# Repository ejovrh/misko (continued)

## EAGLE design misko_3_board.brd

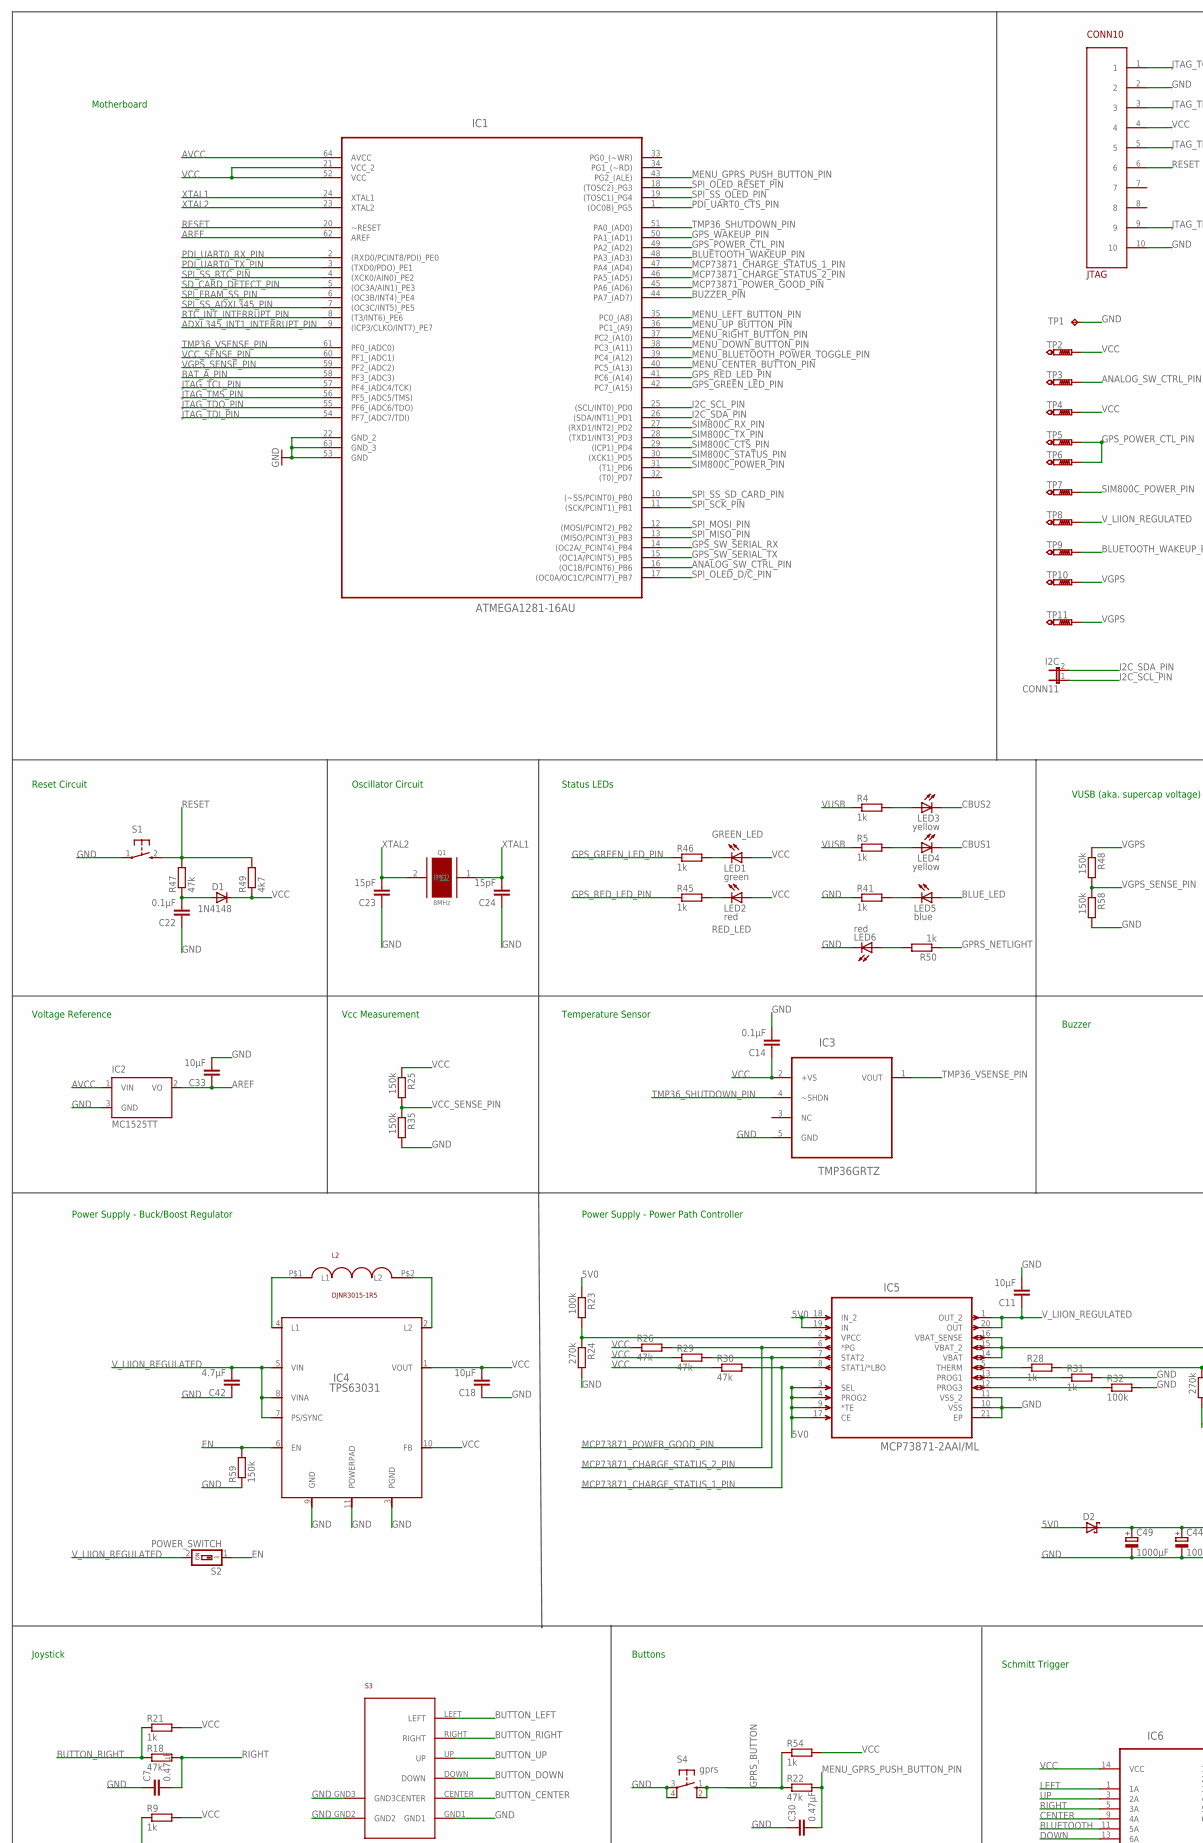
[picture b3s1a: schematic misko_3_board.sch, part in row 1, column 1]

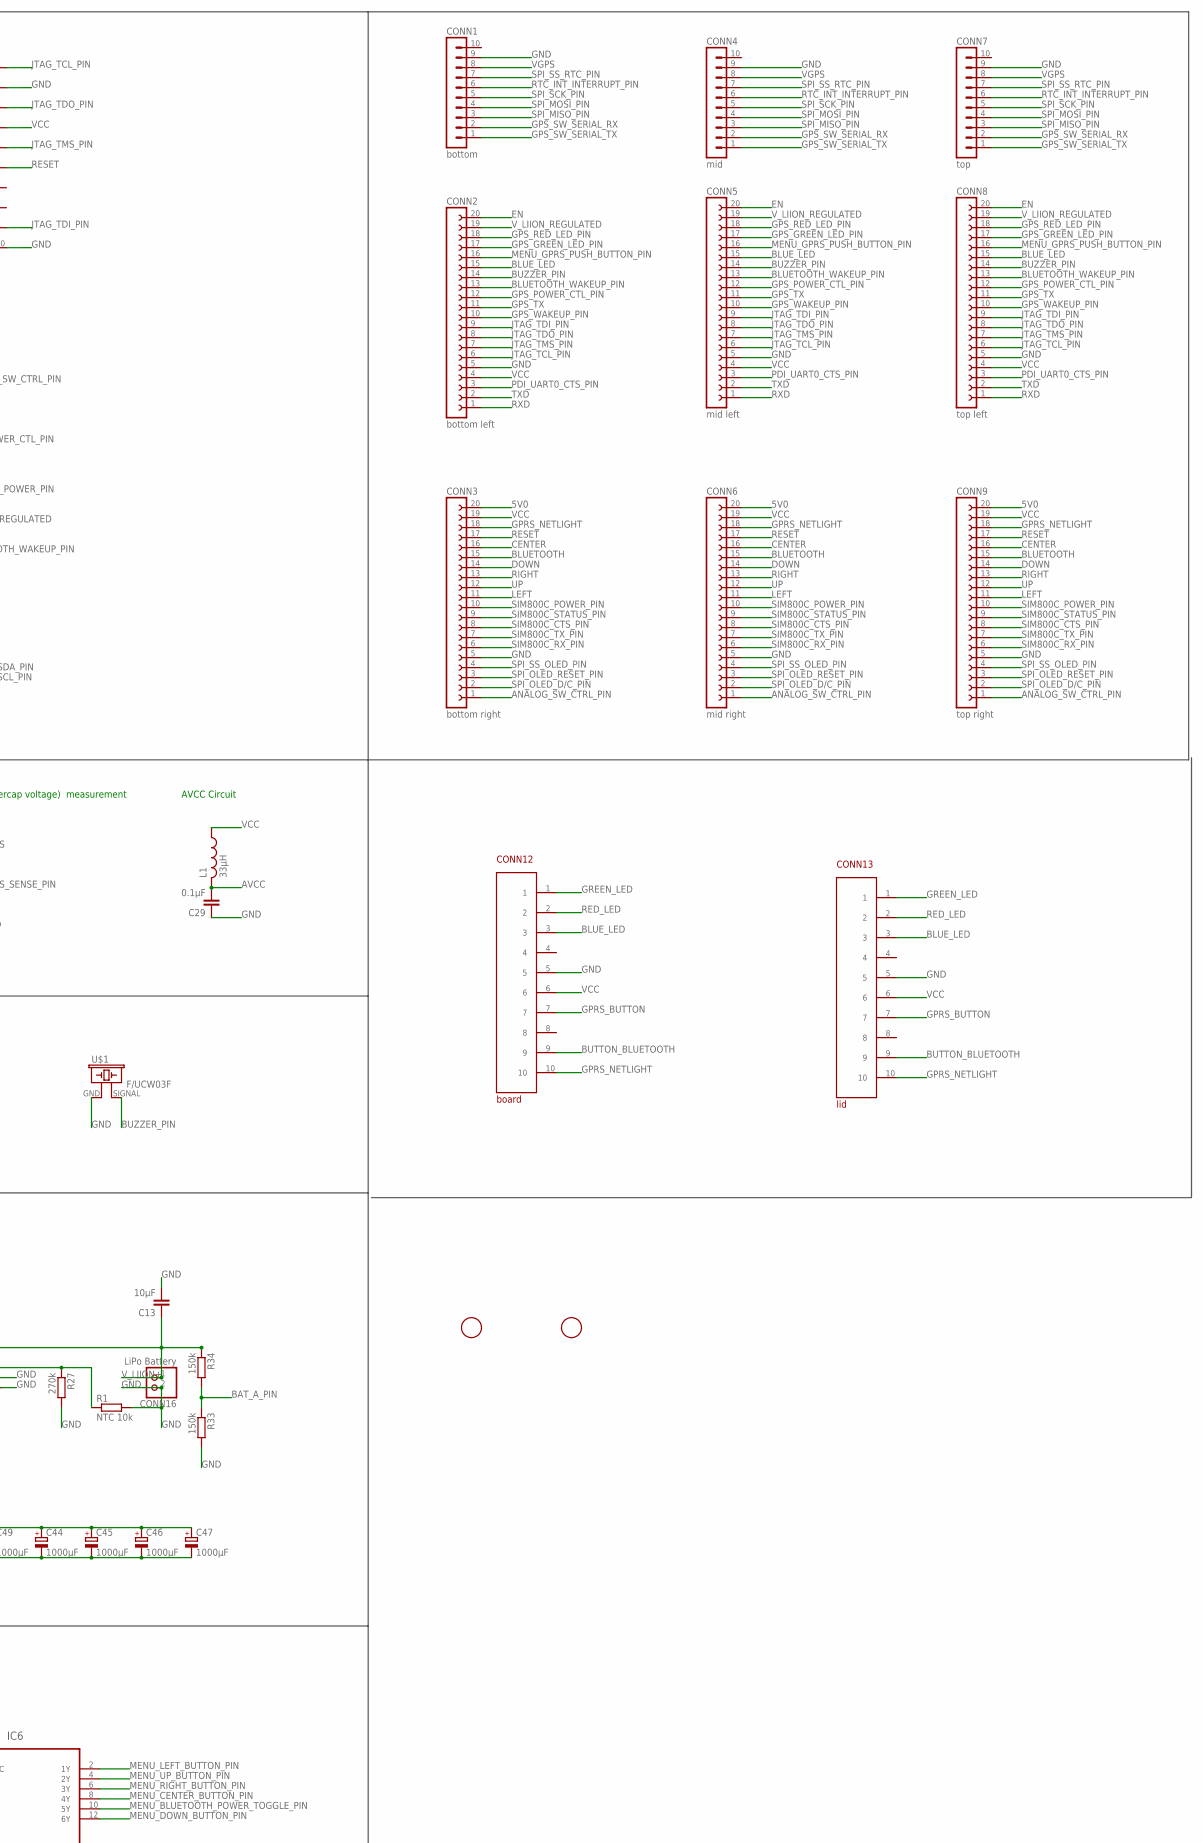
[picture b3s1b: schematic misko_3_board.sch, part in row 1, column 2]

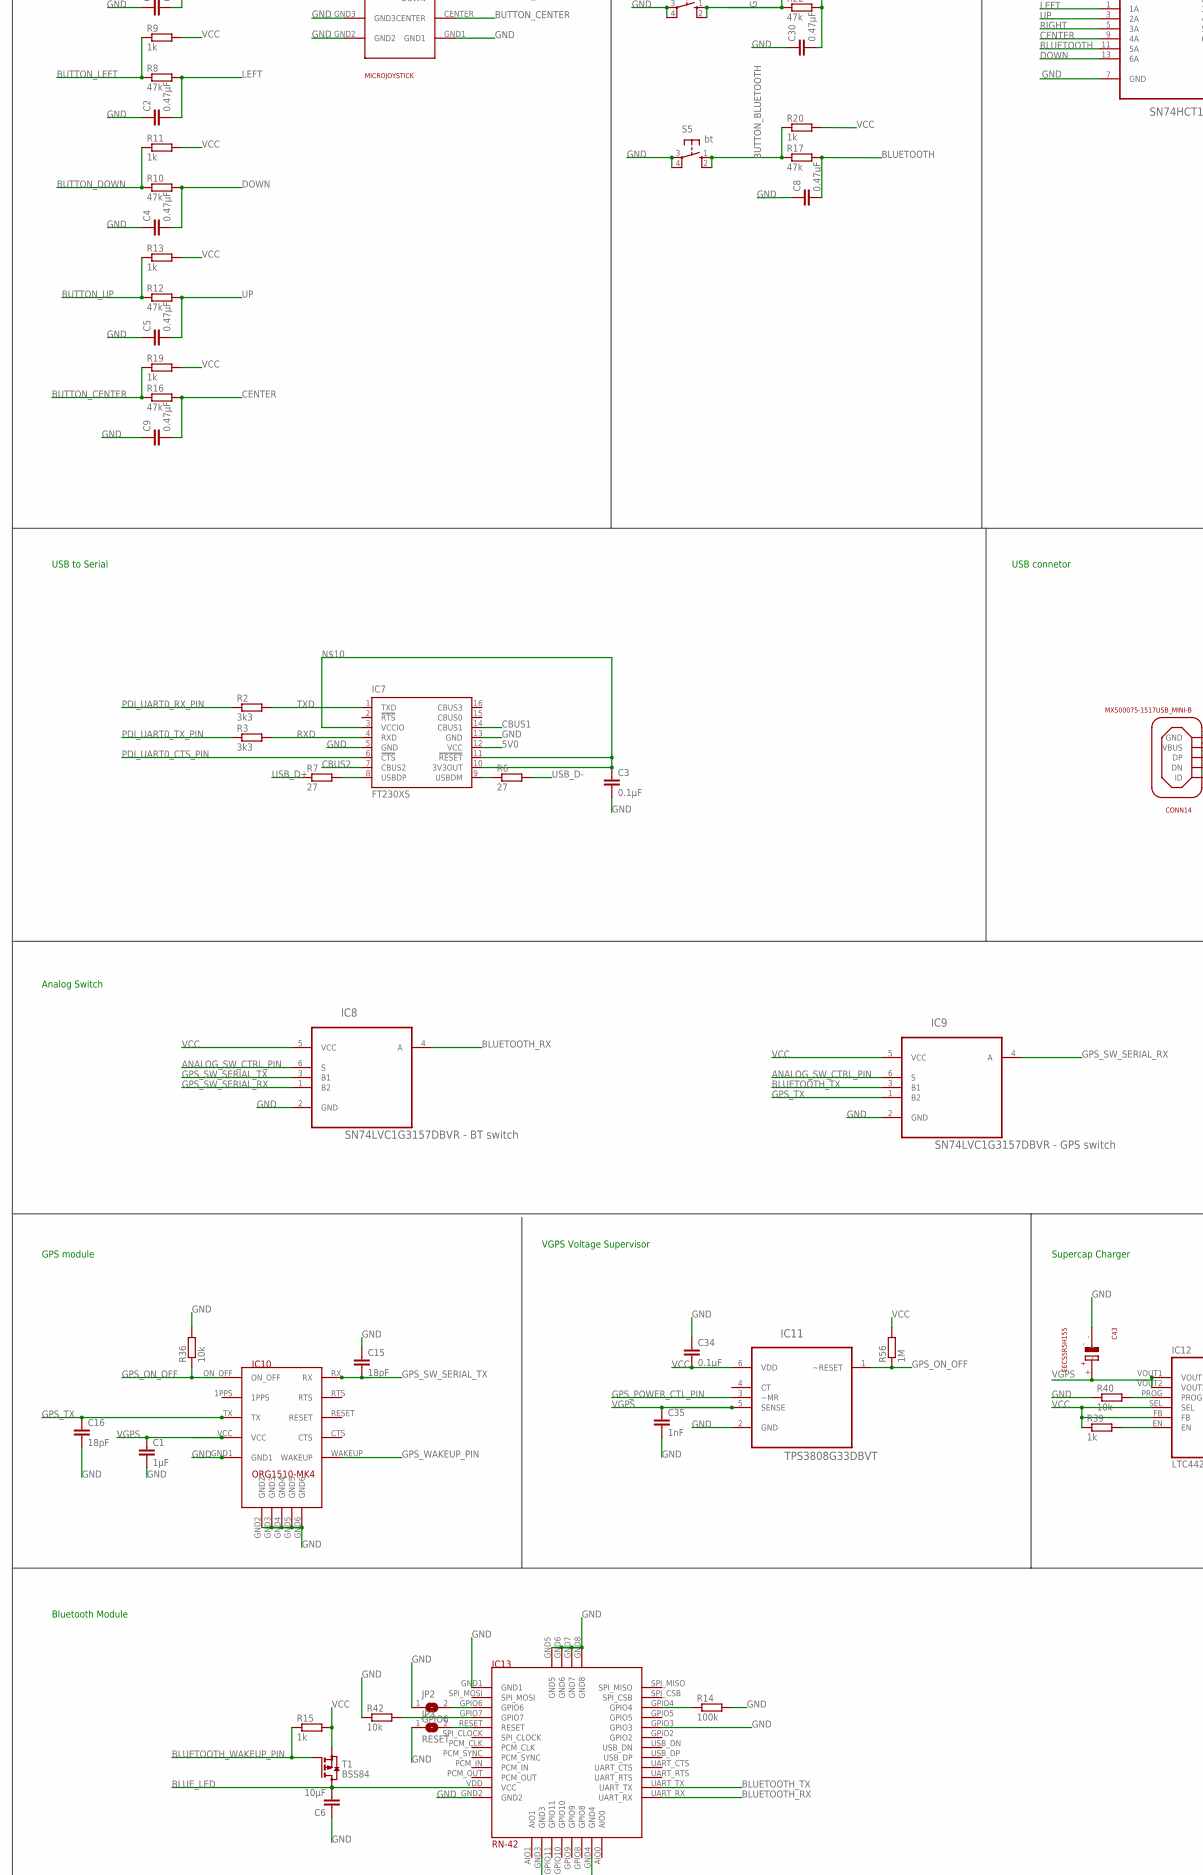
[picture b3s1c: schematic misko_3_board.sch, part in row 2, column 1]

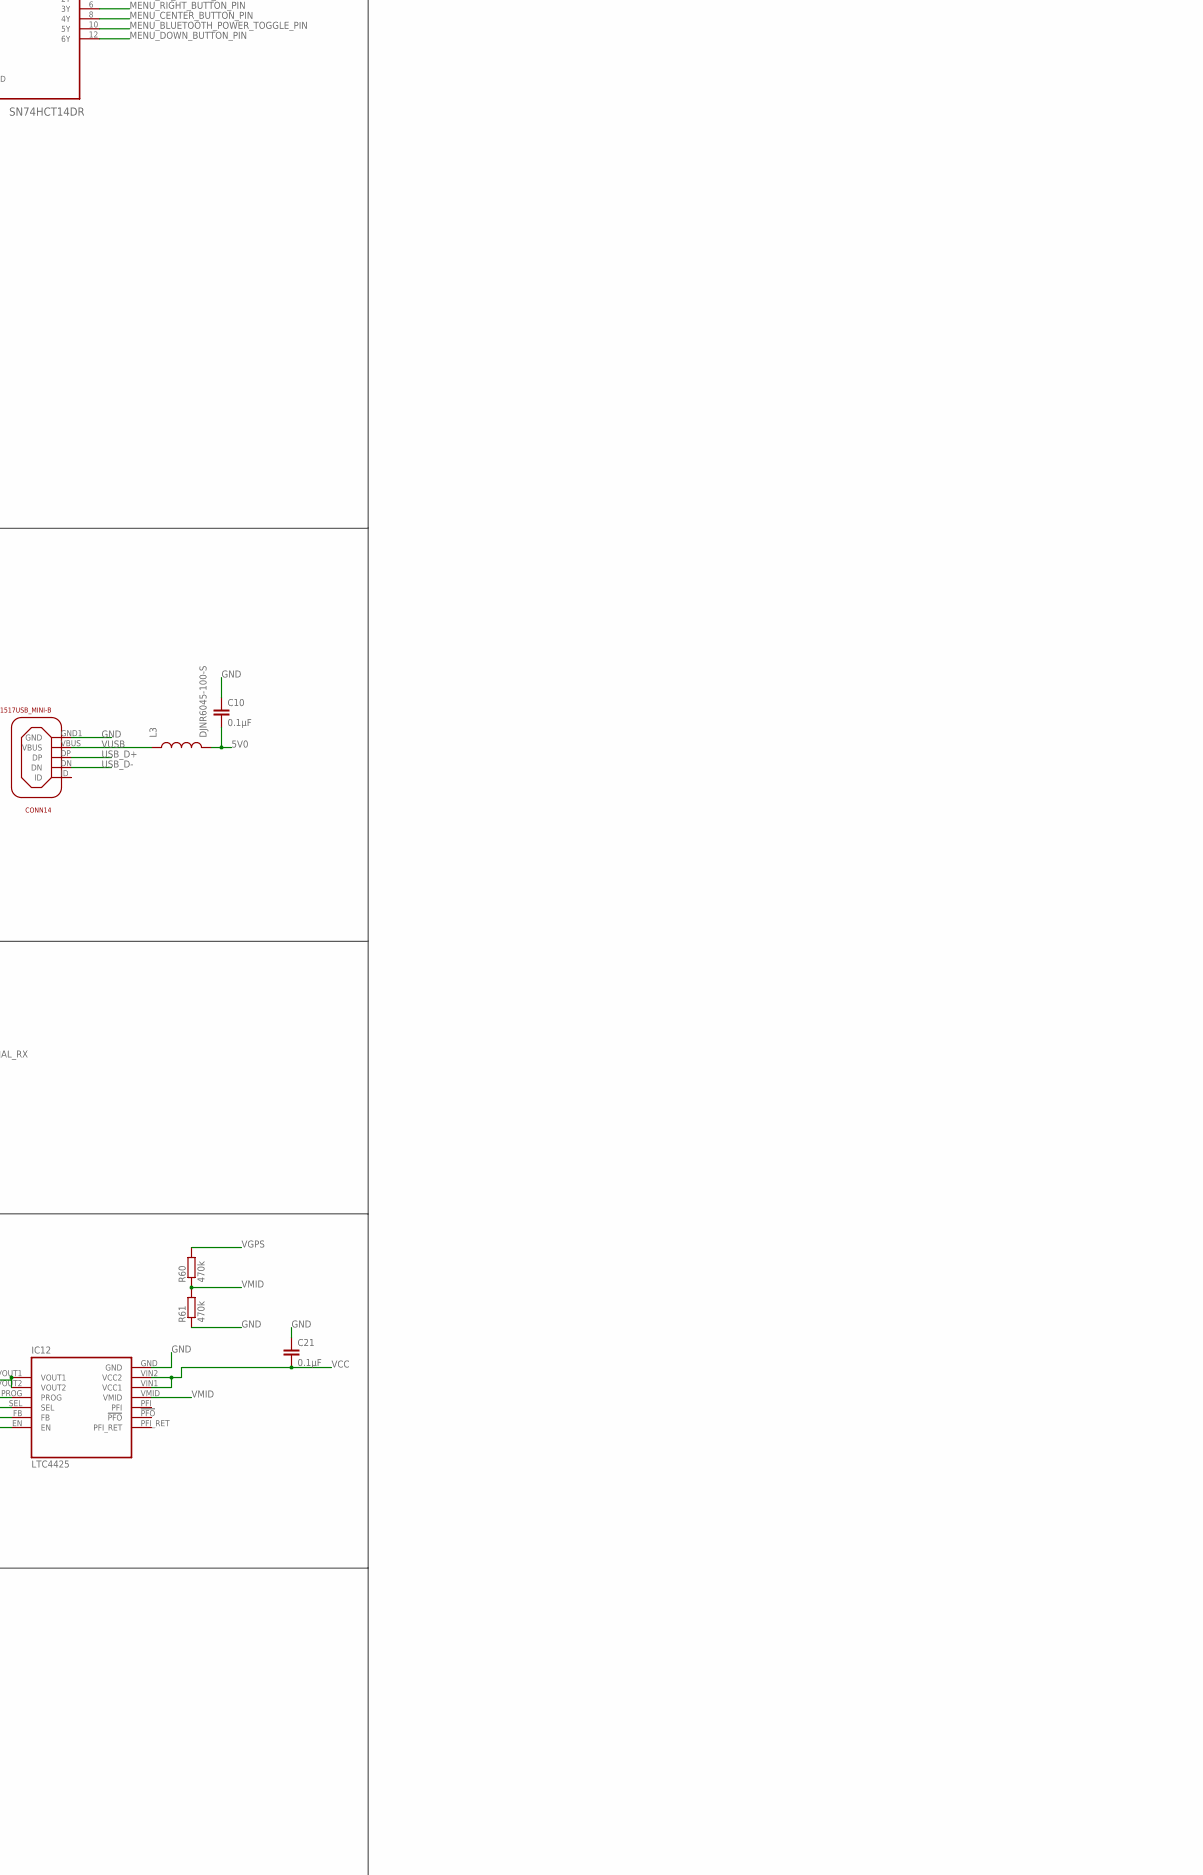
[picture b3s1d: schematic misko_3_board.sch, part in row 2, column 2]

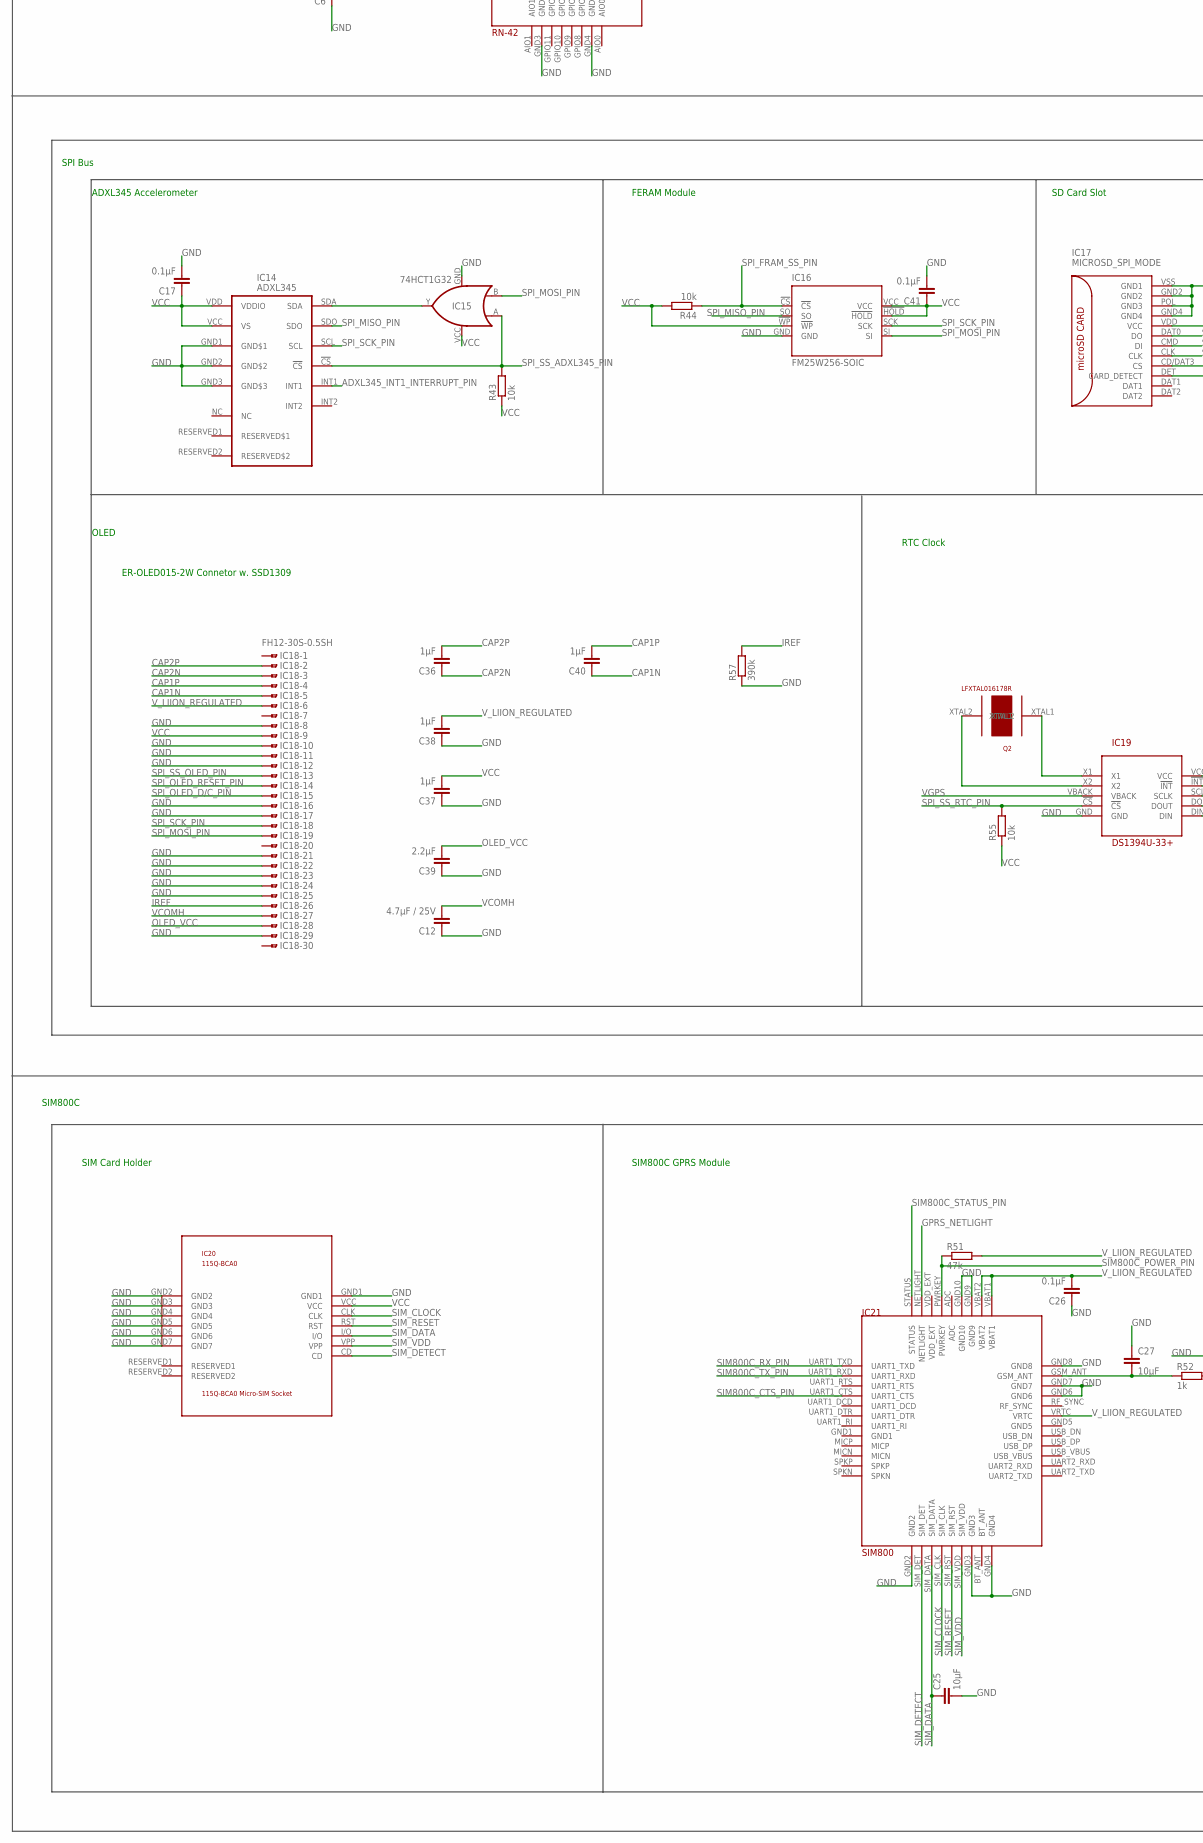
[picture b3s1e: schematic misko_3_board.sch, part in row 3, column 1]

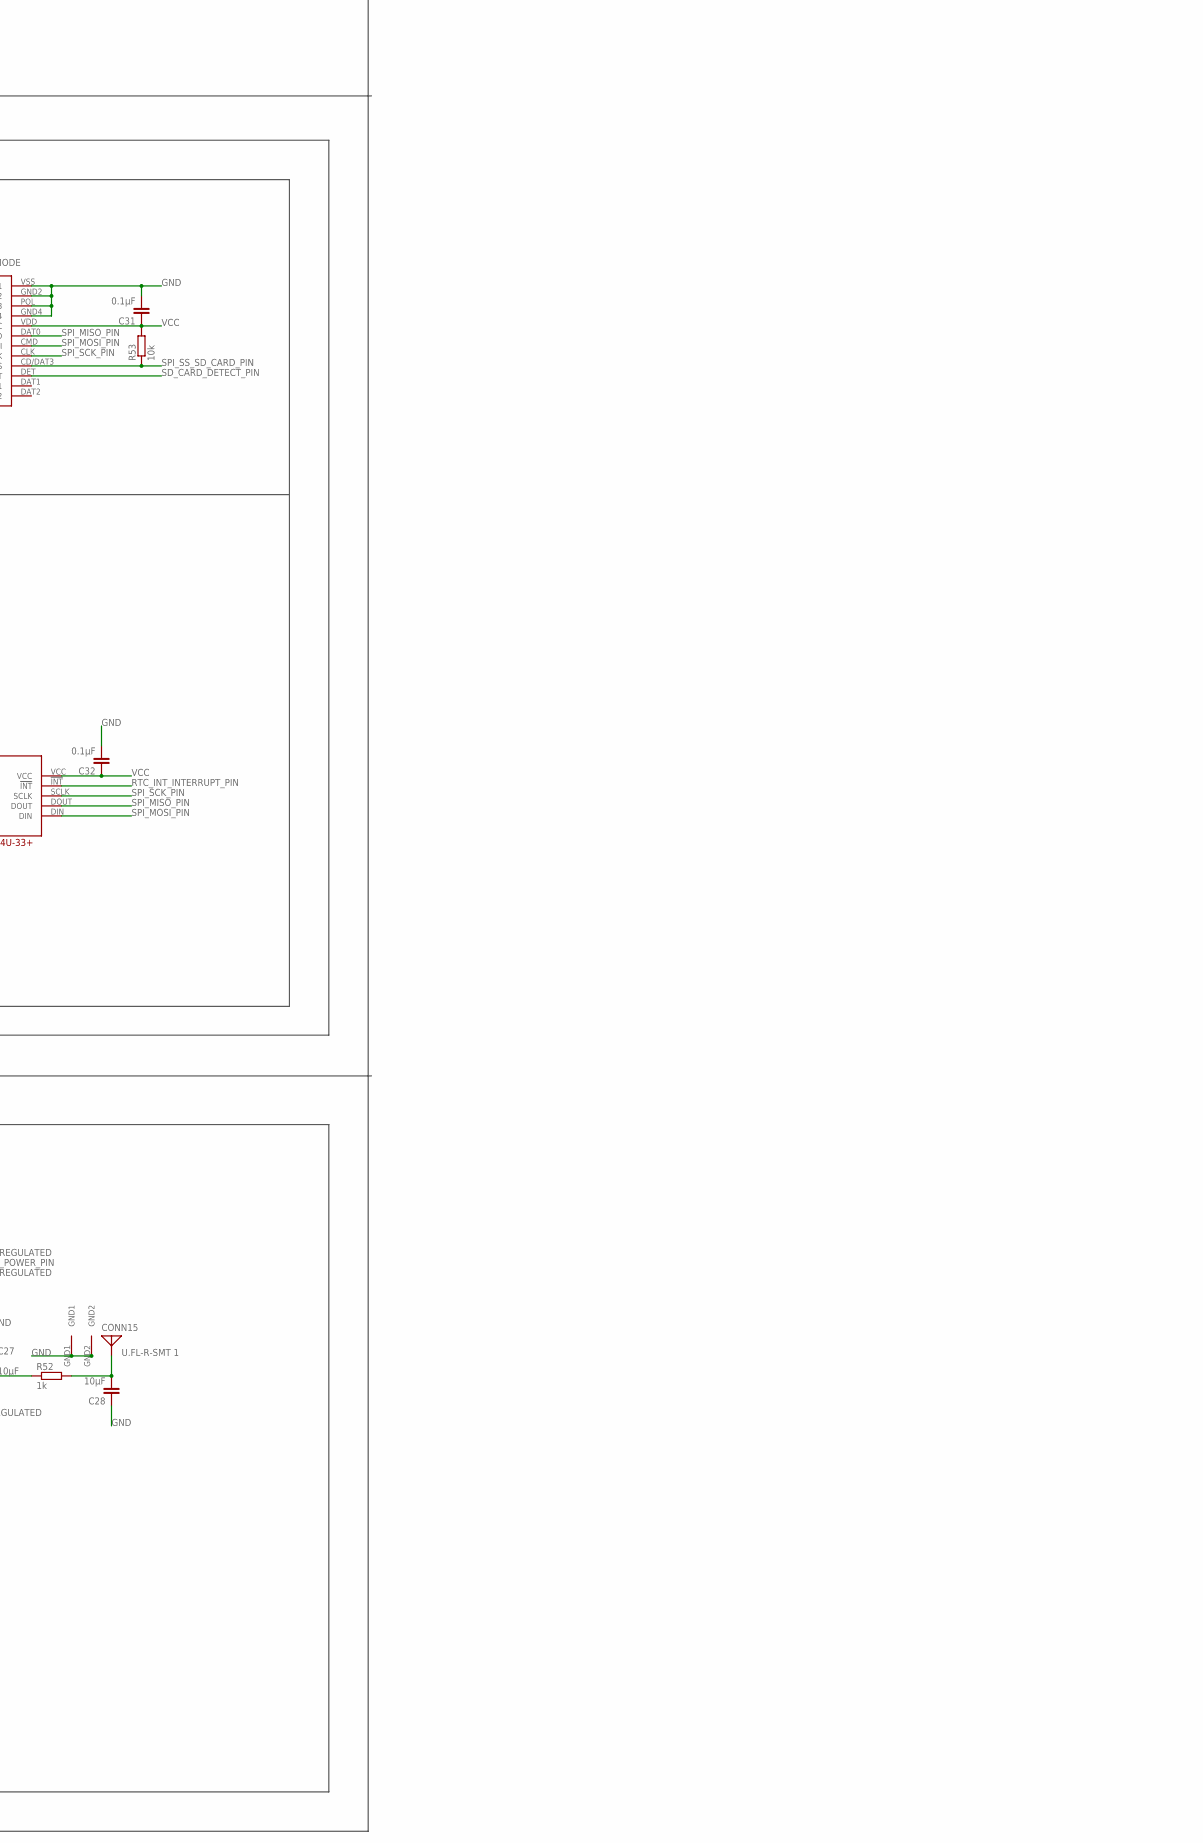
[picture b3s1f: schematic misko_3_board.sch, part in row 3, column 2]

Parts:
C1, C36, C37, C38, C40: 1µF; C0805
C2, C4, C5, C7, C8, C9, C30: 0.47µF; C0805
C3, C10, C14, C17, C21, C22, C26, C29, C31, C32, C34, C41: 0.1µF; C0805
C6, C11, C13, C18, C25, C27, C28, C33: 10µF; C0805
C12: 4.7µF / 25V; C0805
C15, C16: 18pF; C0805
C23, C24: 15pF; C0805
C35: 1nF; C0805
C39: 2.2µF; C0805
C42: 4.7µF; C0805
C43: EECS5R5H155; TH
C44, C45, C46, C47, C49: 1000µF; E22-10
CONN1: bottom; MA10-1
CONN2: bottom left; FE20
CONN3: bottom right; FE20
CONN4: mid; MA10-1
CONN5: mid left; FE20
CONN6: mid right; FE20
CONN7: top; MA10-1
CONN8: top left; FE20
CONN9: top right; FE20
CONN10: JTAG; TH
CONN11: I2C; JP1
CONN12: board; TH
CONN13: lid; TH
CONN14: MX500075-1517USB_MINI-B; TH
CONN15: U.FL-R-SMT 1; SMD
CONN16: LiPo Battery; JST-PH-2-THM-RA
D1: 1N4148; D0805
D2: SCHOTTKY-DIODEF126Z12; DIODE_F126Z12
FI1, FI2: FIDUCIAL; FIDUCIAL_1MM
IC1: ATMEGA1281-16AU; QFP80P1600X1600X120-64N
IC2: MC1525TT; SOT23
IC3: TMP36GRTZ; SOT95P280X145-5N
IC4: TPS63031; NEWPVSON-N10
IC5: MCP73871-2AAI/ML; QFN50P400X400X100-21N
IC6: SN74HCT14DR; SOIC127P600X175-14N
IC7: FT230XS; SSOP16
IC8: SN74LVC1G3157DBVR - BT switch; SOT95P280X145-6N
IC9: SN74LVC1G3157DBVR - GPS switch; SOT95P280X145-6N
IC10: ORG1510-MK4; PACKAGE
IC11: TPS3808G33DBVT; SOT95P280X145-6N
IC12: LTC4425; MSOP
IC13: RN-42
IC14: ADXL345; LGA14
IC15: 74HCT1G32; SOT353/5
IC16: FM25W256-SOIC; SOIC08
IC17: MICROSD_SPI_MODE; MICRO_SD_CONNECTOR
IC18: FH12-30S-0.5SH
IC19: DS1394U-33+; 10UMAX
IC20: 115Q-BCA0
IC21: SIM800; SIM800C
JP2: GPIO6; SJW
JP3: RESET; SJW
L1: 33µH; L0805
L2: DJNR3015-1R5; FFF
L3: DJNR6045-100-S
LED1: green; LED2X5
LED2, LED6: red; LED2X5
LED3, LED4: yellow; CHIPLED_1206
LED5: blue; LED2X5
Q1: 8MHz; QS
Q2: LFXTAL016178R; SMD
R1: NTC 10k; 0204/5
R2, R3: 3k3; R0805
R4, R5, R9, R11, R13, R15, R19, R20, R21, R28, R31, R39, R41, R45, R46, R50, R52, R54: 1k; R0805
R6, R7: 27; R0805
R8, R10, R12, R16, R17, R18, R22, R26, R29, R30, R47, R51: 47k; R0805
R14, R23, R32: 100k; R0805
R24, R27: 270k; R0805
R25, R33, R34, R35, R48, R58, R59: 150k; R0805
R36, R40, R42, R43, R44, R53, R55: 10k; R0805
R49: 4k7; R0805
R56: 1M; R0805
R57: 390k; R0805
R60, R61: 470k; R0805
S1: DTSM-32N-B
S2: POWER_SWITCH; SMS-001
S3: MICROJOYSTICK
S4: gprs; B3F-10XX
S5: bt; B3F-10XX
T1: BSS84; SOT23
TP1: GND; P1-17Y
TP2, TP4: VCC; TP14R
TP3: Analogue Switch CRTL Pin; TP14R
TP5, TP6: GPS Power CTRL Pin; B1,27
TP7: SIM800 Power CTRL Pin; B1,27
TP8: VLiIon Regulated; TP14R
TP9: Bluetooth Wakeup Pin; TP14R
TP10, TP11: VGPS; TP14R
U$1: F/UCW03F; F/UCW03LF

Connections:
5V0: C10.2, CONN3.20, CONN6.20, CONN9.20, D2.A (C), IC5.3 (SEL), IC5.4 (PROG2), IC5.9 (*TE), IC5.17 (CE), IC5.18 (IN_2), IC5.19 (IN), IC7.12 (VCC), L3.P$2 (2), R23.1
ADXL345SDA: IC14.SDA, IC15.Y
ADXL345_INT1_INTERRUPT_PIN: IC1.9 ((ICP3/CLKO/INT7)_PE7), IC14.INT1
ANALOG_SW_CTRL_PIN: CONN3.1, CONN6.1, CONN9.1, IC1.16 ((OC1B/PCINT6)_PB6), IC8.6 (S), IC9.6 (S), TP3.TP
ANTENNA: C28.2, CONN15.SIGNAL (ANT), R52.2
AREF: C33.1, IC1.62 (AREF), IC2.2 (VO)
AVCC: C29.2, IC1.64 (AVCC), IC2.1 (VIN), L1.2
BAT_A_PIN: IC1.58 (PF3_(ADC3)), R33.1, R34.2
BLUETOOTH: C8.2, CONN3.15, CONN6.15, CONN9.15, IC6.11 (5A), R17.2
BLUETOOTH_RX: IC8.4 (A), IC13.UART_RX
BLUETOOTH_TX: IC9.3 (B1), IC13.UART_TX
BLUETOOTH_WAKEUP_PIN: CONN2.13, CONN5.13, CONN8.13, IC1.48 (PA3_(AD3)), R15.1, T1.1 (G), TP9.TP
BLUE_LED: C6.2, CONN2.15, CONN5.15, CONN8.15, CONN12.3, CONN13.3, IC13.VDD (VCC), LED5.A, T1.3 (D)
BT_GPIO6: IC13.GPIO6, JP2.2
BT_LED: LED5.K (C), R41.2
BT_RST: IC13.RESET, JP3.2
BUTTON_BLUETOOTH: CONN12.9, CONN13.9, R17.1, R20.1, S5.1 (S), S5.2 (S1)
BUTTON_CENTER: R16.1, R19.1, S3.CENTER
BUTTON_DOWN: R10.1, R11.1, S3.DOWN
BUTTON_LEFT: R8.1, R9.1, S3.LEFT
BUTTON_RIGHT: R18.1, R21.1, S3.RIGHT
BUTTON_UP: R12.1, R13.1, S3.UP
BUZZER_PIN: CONN2.14, CONN5.14, CONN8.14, IC1.44 (PA7_(AD7)), U$1.SIGNAL
CAP1N: C40.1, IC18.5
CAP1P: C40.2, IC18.4
CAP2N: C36.1, IC18.3
CAP2P: C36.2, IC18.2
CBUS1: IC7.14 (CBUS1), LED4.C
CBUS2: IC7.7 (CBUS2), LED3.C
CENTER: C9.2, CONN3.16, CONN6.16, CONN9.16, IC6.9 (4A), R16.2
DOWN: C4.2, CONN3.14, CONN6.14, CONN9.14, IC6.13 (6A), R10.2
EN: CONN2.20, CONN5.20, CONN8.20, IC4.6 (EN), R59.2, S2.1
GND: C1.2, C2.1, C3.2, C4.1, C5.1, C6.1, C7.1, C8.1, C9.1, C10.1, C11.2, C12.1, C13.2, C14.2, C15.1, C16.2, C17.2, C18.1, C21.1, C22.1, C23.1, C24.1, C25.2, C26.1, C27.1, C28.1, C29.1, C30.1, C31.2, C32.2, C33.2, C34.1, C35.2, C37.1, C38.1, C39.1, C41.2, C42.1, C43.-, C44.-, C45.-, C46.-, C47.-, C49.-, CONN1.9, CONN2.5, CONN3.5, CONN4.9, CONN5.5, CONN6.5, CONN7.9, CONN8.5, CONN9.5, CONN10.2, CONN10.10, CONN12.5, CONN13.5, CONN14.GND1 (GND), CONN15.GND1, CONN15.GND2, CONN16.2 (1), IC1.22 (GND_2), IC1.53 (GND), IC1.63 (GND_3), IC2.3 (GND), IC3.5 (GND), IC4.3 (PGND), IC4.9 (GND), IC4.11 (POWERPAD), IC5.10 (VSS), IC5.11 (VSS_2), IC5.21 (EP), IC6.7 (GND), IC7.5 (GND), IC7.13 (GND), IC8.2 (GND), IC9.2 (GND), IC10.GND1, IC10.GND2, IC10.GND3, IC10.GND4, IC10.GND5, IC10.GND6, IC11.2 (GND), IC12.GND, IC13.GND1, IC13.GND2, IC13.GND3, IC13.GND4, IC13.GND5, IC13.GND6, IC13.GND7, IC13.GND8, IC13.GPIO3, IC14.GND1 (GND$1), IC14.GND2 (GND$2), IC14.GND3 (GND$3), IC15.GND, IC16.GND, IC17.GND2, IC17.GND4, IC17.POL (GND3), IC17.VSS (GND1), IC18.8, IC18.10, IC18.11, IC18.12, IC18.16, IC18.17, IC18.21, IC18.22, IC18.23, IC18.24, IC18.25, IC18.29, IC19.GND, IC20.GND1, IC20.GND2, IC20.GND3, IC20.GND4, IC20.GND5, IC20.GND6, IC20.GND7, IC21.GND2, IC21.GND3, IC21.GND4, IC21.GND6, IC21.GND7, IC21.GND8, IC21.GND9, IC21.GND10, JP2.1, JP3.1, LED6.K (C), R1.2, R14.2, R24.2, R27.2, R31.2, R32.2, R33.2, R35.2, R36.2, R40.1, R41.1, R42.1, R57.1, R58.2, R59.1, R61.1, S1.1, S3.GND1, S3.GND2, S3.GND3, S4.3, S4.4 (P1), S5.3, S5.4 (P1), TP1.TP, U$1.GND
GPIO4: IC13.GPIO4, R14.1
GPIO7: IC13.GPIO7, R42.2
GPRS_BUTTON: CONN12.7, CONN13.7, R22.1, R54.1, S4.1 (S), S4.2 (S1)
GPRS_LED: LED6.A, R50.2
GPRS_NETLIGHT: CONN3.18, CONN6.18, CONN9.18, CONN12.10, CONN13.10, IC21.NETLIGHT, R50.1
GPS_GREEN_LED_PIN: CONN2.17, CONN5.17, CONN8.17, IC1.42 (PC7_(A15)), R46.1
GPS_ON_OFF: IC10.ON_OFF, IC11.1 (~RESET), R36.1, R56.1
GPS_POWER_CTL_PIN: CONN2.12, CONN5.12, CONN8.12, IC1.49 (PA2_(AD2)), IC11.3 (~MR), TP5.TP, TP6.TP
GPS_RED_LED_PIN: CONN2.18, CONN5.18, CONN8.18, IC1.41 (PC6_(A14)), R45.1
GPS_SW_SERIAL_RX: CONN1.2, CONN4.2, CONN7.2, IC1.14 ((OC2A/_PCINT4)_PB4), IC8.1 (B2), IC9.4 (A)
GPS_SW_SERIAL_TX: C15.2, CONN1.1, CONN4.1, CONN7.1, IC1.15 ((OC1A/PCINT5)_PB5), IC8.3 (B1), IC10.RX
GPS_TX: C16.1, CONN2.11, CONN5.11, CONN8.11, IC9.1 (B2), IC10.TX
GPS_WAKEUP_PIN: CONN2.10, CONN5.10, CONN8.10, IC1.50 (PA1_(AD1)), IC10.WAKEUP
GREEN_LED: CONN12.1, CONN13.1, LED1.K (C), R46.2
GSM_ANT: C27.2, IC21.GSM_ANT, R52.1
I2C_SCL_PIN: CONN11.1, IC1.25 ((SCL/INT0)_PD0)
I2C_SDA_PIN: CONN11.2, IC1.26 ((SDA/INT1)_PD1)
IREF: IC18.26, R57.2
JTAG_TCL_PIN: CONN2.6, CONN5.6, CONN8.6, CONN10.1, IC1.57 (PF4_(ADC4/TCK))
JTAG_TDI_PIN: CONN2.9, CONN5.9, CONN8.9, CONN10.9, IC1.54 (PF7_(ADC7/TDI))
JTAG_TDO_PIN: CONN2.8, CONN5.8, CONN8.8, CONN10.3, IC1.55 (PF6_(ADC6/TDO))
JTAG_TMS_PIN: CONN2.7, CONN5.7, CONN8.7, CONN10.5, IC1.56 (PF5_(ADC5/TMS))
L1: IC4.4 (L1), L2.P$1 (L1)
L2: IC4.2 (L2), L2.P$2 (L2)
LEFT: C2.2, CONN3.11, CONN6.11, CONN9.11, IC6.1 (1A), R8.2
LTC4425_EN: IC12.EN, R39.2
LTC4425_PROG: IC12.PROG, R40.2
MCP73871_CHARGE_STATUS_1_PIN: IC1.47 (PA4_(AD4)), IC5.8 (STAT1/*LBO), R30.2
MCP73871_CHARGE_STATUS_2_PIN: IC1.46 (PA5_(AD5)), IC5.7 (STAT2), R29.2
MCP73871_POWER_GOOD_PIN: IC1.45 (PA6_(AD6)), IC5.6 (*PG), R26.2
MENU_BLUETOOTH_POWER_TOGGLE_PIN: IC1.39 (PC4_(A12)), IC6.10 (5Y)
MENU_CENTER_BUTTON_PIN: IC1.40 (PC5_(A13)), IC6.8 (4Y)
MENU_DOWN_BUTTON_PIN: IC1.38 (PC3_(A11)), IC6.12 (6Y)
MENU_GPRS_PUSH_BUTTON_PIN: C30.2, CONN2.16, CONN5.16, CONN8.16, IC1.43 (PG2_(ALE)), R22.2
MENU_LEFT_BUTTON_PIN: IC1.35 (PC0_(A8)), IC6.2 (1Y)
MENU_RIGHT_BUTTON_PIN: IC1.37 (PC2_(A10)), IC6.6 (3Y)
MENU_UP_BUTTON_PIN: IC1.36 (PC1_(A9)), IC6.4 (2Y)
unnamed: C44.+, C45.+, C46.+, C47.+, C49.+, D2.C (A)
unnamed: C3.1, IC7.3 (VCCIO), IC7.10 (3V3OUT), IC7.11 (!RESET)
unnamed: R1.1, R27.1, R28.2
unnamed: C22.2, D1.A, R47.1
OLED_VCC: C39.2, IC18.28
PDI_UART0_CTS_PIN: CONN2.3, CONN5.3, CONN8.3, IC1.1 ((OC0B)_PG5), IC7.6 (!CTS)
PDI_UART0_RX_PIN: IC1.2 ((RXD0/PCINT8/PDI)_PE0), R2.1
PDI_UART0_TX_PIN: IC1.3 ((TXD0/PDO)_PE1), R3.1
PFI_RET: IC12.PFI_RET
PROG1: IC5.13 (PROG1), R31.1
PROG3: IC5.12 (PROG3), R32.1
RED_LED: CONN12.2, CONN13.2, LED2.K (C), R45.2
RESET: CONN3.17, CONN6.17, CONN9.17, CONN10.6, IC1.20 (~RESET), R47.2, R49.2, S1.2
RIGHT: C7.2, CONN3.13, CONN6.13, CONN9.13, IC6.5 (3A), R18.2
RTC_INT_INTERRUPT_PIN: CONN1.6, CONN4.6, CONN7.6, IC1.8 ((T3/INT6)_PE6), IC19.!INT!
RTC_XTAL1: IC19.X1, Q2.XTAL1
RTC_XTAL2: IC19.X2, Q2.XTAL2
RXD: CONN2.1, CONN5.1, CONN8.1, IC7.4 (RXD), R3.2
SD_CARD_DETECT_PIN: IC1.5 ((OC3A/AIN1)_PE3), IC17.DET (CARD_DETECT)
SIM800C_CTS_PIN: CONN3.8, CONN6.8, CONN9.8, IC1.29 ((ICP1)_PD4), IC21.UART1_CTS
SIM800C_POWER_PIN: CONN3.10, CONN6.10, CONN9.10, IC1.31 ((T1)_PD6), IC21.PWRKEY, R51.1, TP7.TP
SIM800C_RX_PIN: CONN3.6, CONN6.6, CONN9.6, IC1.27 ((RXD1/INT2)_PD2), IC21.UART1_TXD
SIM800C_STATUS_PIN: CONN3.9, CONN6.9, CONN9.9, IC1.30 ((XCK1)_PD5), IC21.STATUS
SIM800C_TX_PIN: CONN3.7, CONN6.7, CONN9.7, IC1.28 ((TXD1/INT3)_PD3), IC21.UART1_RXD
SIM_CLOCK: IC20.CLK, IC21.SIM_CLK
SIM_DATA: C25.1, IC20.I/O, IC21.SIM_DATA
SIM_DETECT: IC20.CD, IC21.SIM_DET
SIM_RESET: IC20.RST, IC21.SIM_RST
SIM_VDD: IC20.VPP, IC21.SIM_VDD
SPI_FRAM_SS_PIN: IC1.6 ((OC3B/INT4)_PE4), IC16.!CS!, R44.1
SPI_MISO_PIN: CONN1.3, CONN4.3, CONN7.3, IC1.13 ((MISO/PCINT3)_PB3), IC14.SDO, IC16.SO, IC17.DAT0 (DO), IC19.DOUT
SPI_MOSI_PIN: CONN1.4, CONN4.4, CONN7.4, IC1.12 ((MOSI/PCINT2)_PB2), IC15.B, IC16.SI, IC17.CMD (DI), IC18.19, IC19.DIN
SPI_OLED_D/C_PIN: CONN3.2, CONN6.2, CONN9.2, IC1.17 ((OC0A/OC1C/PCINT7)_PB7), IC18.15
SPI_OLED_RESET_PIN: CONN3.3, CONN6.3, CONN9.3, IC1.18 ((TOSC2)_PG3), IC18.14
SPI_SCK_PIN: CONN1.5, CONN4.5, CONN7.5, IC1.11 ((SCK/PCINT1)_PB1), IC14.SCL, IC16.SCK, IC17.CLK, IC18.18, IC19.SCLK
SPI_SS_ADXL345_PIN: IC1.7 ((OC3C/INT5)_PE5), IC14.!CS!, IC15.A, R43.2
SPI_SS_OLED_PIN: CONN3.4, CONN6.4, CONN9.4, IC1.19 ((TOSC1)_PG4), IC18.13
SPI_SS_RTC_PIN: CONN1.7, CONN4.7, CONN7.7, IC1.4 ((XCK0/AIN0)_PE2), IC19.!CS!, R55.2
SPI_SS_SD_CARD_PIN: IC1.10 ((~SS/PCINT0)_PB0), IC17.CD/DAT3 (CS), R53.1
THERM: IC5.5 (THERM), R28.1
TMP36_SHUTDOWN_PIN: IC1.51 (PA0_(AD0)), IC3.4 (~SHDN)
TMP36_VSENSE_PIN: IC1.61 (PF0_(ADC0)), IC3.1 (VOUT)
TXD: CONN2.2, CONN5.2, CONN8.2, IC7.1 (TXD), R2.2
UP: C5.2, CONN3.12, CONN6.12, CONN9.12, IC6.3 (2A), R12.2
USBDM: IC7.9 (USBDM), R6.1
USBDP: IC7.8 (USBDP), R7.2
USB_D+: CONN14.DP, R7.1
USB_D-: CONN14.DN, R6.2
USB_RX_LED: LED3.A, R4.2
USB_TX_LED: LED4.A, R5.2
VCC: C14.1, C17.1, C18.2, C21.2, C31.1, C32.1, C34.2, C37.2, C41.1, CONN2.4, CONN3.19, CONN5.4, CONN6.19, CONN8.4, CONN9.19, CONN10.4, CONN12.6, CONN13.6, D1.C, IC1.21 (VCC_2), IC1.52 (VCC), IC3.2 (+VS), IC4.1 (VOUT), IC4.10 (FB), IC6.14 (VCC), IC8.5 (VCC), IC9.5 (VCC), IC11.6 (VDD), IC12.FB, IC12.SEL, IC12.VIN1 (VCC1), IC12.VIN2 (VCC2), IC14.VCC (VS), IC14.VDD (VDDIO), IC15.VCC, IC16.!HOLD!, IC16.!WP!, IC16.VCC, IC17.VDD (VCC), IC18.9, IC19.VCC, IC20.VCC, L1.1, LED1.A, LED2.A, R9.2, R11.2, R13.2, R15.2, R19.2, R20.2, R21.2, R25.1, R26.1, R29.1, R30.1, R39.1, R43.1, R44.2, R49.1, R53.2, R54.2, R55.1, R56.2, T1.2 (S), TP2.TP, TP4.TP
VCC_SENSE_PIN: IC1.60 (PF1_(ADC1)), R25.2, R35.1
VCOMH: C12.2, IC18.27
VGPS: C1.1, C35.1, C43.+, CONN1.8, CONN4.8, CONN7.8, IC10.VCC, IC11.5 (SENSE), IC12.VOUT1, IC12.VOUT2, IC19.VBACK, R48.1, R60.2, TP10.TP, TP11.TP
VGPS_SENSE_PIN: IC1.59 (PF2_(ADC2)), R48.2, R58.1
VMID: IC12.VMID, R60.1, R61.2
VPCC: IC5.2 (VPCC), R23.2, R24.1
VUSB: CONN14.VBUS, L3.P$1 (1), R4.1, R5.1
V_LIION+: C13.1, CONN16.1 (2), IC5.14 (VBAT), IC5.15 (VBAT_2), IC5.16 (VBAT_SENSE), R34.1
V_LIION_REGULATED: C11.1, C26.2, C38.2, C42.2, CONN2.19, CONN5.19, CONN8.19, IC4.5 (VIN), IC4.7 (PS/SYNC), IC4.8 (VINA), IC5.1 (OUT_2), IC5.20 (OUT), IC18.6, IC21.VBAT1, IC21.VBAT2, IC21.VRTC, R51.2, S2.2, TP8.TP
XTAL1: C24.2, IC1.24 (XTAL1), Q1.1
XTAL2: C23.2, IC1.23 (XTAL2), Q1.2

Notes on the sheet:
Joystick
Temperature Sensor
Analog Switch
Motherboard
Voltage Reference
Vcc Measurement
Power Supply - Buck/Boost Regulator
Power Supply - Power Path Controller
USB to Serial
GPS module
Supercap Charger
Bluetooth Module
SPI Bus
ADXL345 Accelerometer
FERAM Module
Status LEDs
Reset Circuit
Oscillator Circuit
AVCC Circuit
SD Card Slot
OLED
ER-OLED015-2W Connetor w. SSD1309
SIM800C
SIM Card Holder
SIM800C GPRS Module
VUSB (aka. supercap voltage) measurement
RTC Clock
Buttons
Schmitt Trigger
USB connetor
VGPS Voltage Supervisor
Buzzer
